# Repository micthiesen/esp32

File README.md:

# ESP32 Multi-Module Project

A modular ESP32 development environment with support for multiple main modules, configured for the Zed editor.

## Included Components

- **ESP-IDF v5.4** (as git submodule - ensures version consistency)
- **Build system** - CMake with multi-module support
- **Code quality** - clang-format, clang-tidy, clangd configuration with lint.sh
- **Zed integration** - Tasks, settings, and LSP setup
- **WiFi helper** - Secure credential management with wifi_helper component
- **Dynamic module selection** - Automatic discovery of main modules
- **Self-contained** - No global ESP-IDF installation required

## Project Structure

```
esp32/
├── .zed/                 # Zed editor configuration
│   ├── settings.json     # LSP and formatting settings
│   └── tasks.json        # Build/flash/monitor tasks
├── main/                 # Main modules directory
│   ├── main_blink.c      # LED blink example
│   ├── main_wifi.c       # WiFi connection example
│   ├── main_sensor.c     # Sensor reading example
│   └── wifi_config.h     # WiFi credentials (git-ignored)
├── components/           # Shared components
│   ├── helpers/          # Helper functions library
│   └── wifi_helper/      # WiFi connection component
├── CMakeLists.txt        # Root CMake configuration
├── .clang-format         # C/C++ formatting rules
├── .clangd               # LSP configuration
└── select_main.sh        # Module selection script
```

## Setup Instructions

### 1. Clone with Submodules

When cloning this repository, use `--recursive` to get the ESP-IDF submodule:

```bash
git clone --recursive <your-repo-url>
cd esp32
```

Or if you already cloned without `--recursive`:

```bash
git submodule update --init --recursive
```

### 2. Install ESP-IDF Tools

```bash
cd esp-idf
./install.sh esp32,esp32s3,esp32c3
cd ..
```

### 3. Set up Environment Alias

Add this to your shell profile (~/.zshrc or ~/.bashrc):

```bash
alias get_idf='. ./esp-idf/export.sh'
```

### 4. Initialize ESP-IDF for Each Session

Before working with ESP32, run (from project root):
```bash
get_idf
```

## Building Projects

### Method 1: Using Selection Script (Recommended)

```bash
./select_main.sh
# The script automatically discovers available modules
# Follow the prompts to select a module
# The selection is saved and persists across sessions
```

The script automatically discovers all `main_*.c` files and extracts descriptions from the code. No need to update the script when adding new modules!

### Method 2: Manual Module Selection

```bash
# Write the module name directly to the file
echo "wifi" > .main_module

# Then build normally
get_idf
idf.py build
```

### Method 3: Direct Build

The system automatically uses the currently selected module:

```bash
get_idf
idf.py build  # Uses whatever is in .main_module
```

## Zed Editor Tasks

Open the Command Palette (Cmd+Shift+P) and search for "task" to see available tasks:

### Build & Flash Tasks
- **Build** - Compile the current module
- **Flash** - Upload to ESP32
- **Monitor** - View serial output
- **Build & Flash** - Compile and upload
- **Build & Flash (Production)** - Optimized production build and flash
- **Build, Flash & Monitor** - All in one
- **Clean** - Remove build artifacts

### Module Management
- **Select Main Module** - Interactive module selection
- **Show Current Module** - Display currently selected module

### Configuration
- **Menuconfig** - Configure ESP32 settings
- **Set Target** - Switch between ESP32/ESP32-S3/ESP32-C3

### Analysis & Debug
- **Size Analysis** - Analyze binary size
- **Component Size Analysis** - Detailed size breakdown
- **Open Serial Monitor** - Monitor serial output
- **Erase Flash** - Completely erase flash memory

## Common Commands

```bash
# Set target chip
idf.py set-target esp32    # or esp32s3, esp32c3

# Configure project
idf.py menuconfig

# Build project
idf.py build

# Flash to device
idf.py flash

# Monitor serial output
idf.py monitor

# Combined commands
idf.py build flash monitor

# Clean build
idf.py fullclean

# Size analysis
idf.py size
idf.py size-components
```

## Module Selection System

The project uses a **file-based module selection** system:

- Current module is stored in `.main_module` file
- This file is user-specific (not committed to git)
- All build commands automatically use the selected module
- Module selection persists across terminal sessions and IDE restarts

### Current Module Status

```bash
# Check current module
cat .main_module

# Or use the task: "Show Current Module" in Zed
```

## Adding New Main Modules

1. Create a new file `main/main_yourmodule.c`
2. Include the app_main() function
3. Add a descriptive ESP_LOGI line (optional, for better descriptions):
   ```c
   ESP_LOGI(TAG, "Your module description starting...");
   ```
4. Select your module: `./select_main.sh` (it will auto-discover your new module)
5. Build: `idf.py build`

The module selection script automatically discovers new modules - no configuration needed!

## WiFi Module Configuration

The WiFi module uses a secure configuration system to keep credentials out of version control:

1. **Copy the template file:**
   ```bash
   cp main/wifi_config.h.template main/wifi_config.h
   ```

2. **Edit your WiFi credentials:**
   ```bash
   # Edit with your preferred editor
   nano main/wifi_config.h
   # or
   code main/wifi_config.h
   ```

3. **Update the configuration:**
   ```c
   #define WIFI_SSID "Your_Actual_WiFi_Name"
   #define WIFI_PASS "Your_Actual_Password"
   ```

4. **Build and flash:**
   ```bash
   idf.py build flash monitor
   ```

**Note:** The `wifi_config.h` file is git-ignored to keep your credentials secure. Each developer needs to create their own configuration file.

### Advanced WiFi Settings

You can customize additional WiFi parameters in `wifi_config.h`:

```c
// Connection settings
#define WIFI_MAX_RETRY 10                    // Retry attempts
#define WIFI_CONNECT_TIMEOUT_MS 15000        // Timeout in milliseconds

// Security settings
#define WIFI_AUTH_MODE WIFI_AUTH_WPA2_PSK    // Authentication mode
```

Available authentication modes:
- `WIFI_AUTH_OPEN` - No security (not recommended)
- `WIFI_AUTH_WEP` - WEP (legacy, not recommended)
- `WIFI_AUTH_WPA_PSK` - WPA-PSK
- `WIFI_AUTH_WPA2_PSK` - WPA2-PSK (recommended)
- `WIFI_AUTH_WPA2_WPA3_PSK` - WPA2/WPA3 mixed mode

## Troubleshooting

### Port Access Issues
If you get permission errors accessing the serial port:
```bash
sudo usermod -a -G dialout $USER  # Linux
# On macOS, the user should already have access
```

### Build Errors
1. Ensure ESP-IDF is sourced: `get_idf`
2. Clean and rebuild: `idf.py fullclean && idf.py build`
3. Check target matches your board: `idf.py set-target esp32`

### Zed LSP Issues
1. Ensure you've run the initial setup: `get_idf` from the project root
2. Restart Zed from the project directory: `zed .`
3. The project now uses a local ESP-IDF submodule for consistency

### Module Selection Issues
- If build fails with "No such file", check current module: `cat .main_module`
- Run `./select_main.sh` to select a valid module
- Verify the main file exists: `ls main/main_$(cat .main_module).c`

## Helper Functions

The `helpers` component provides utility functions:

- **Timing**: `delay_ms()`, `get_time_ms()`
- **LED Control**: `led_init()`, `led_on()`, `led_off()`, `led_toggle()`
- **Debug**: `hex_dump()`
- **Math**: `map_range()`, `constrain()`

Include in your module:
```c
#include "helpers.h"
```

## Code Quality and Linting

The project includes a comprehensive linting system to maintain code quality:

### Running Code Quality Checks

```bash
./lint.sh
```

The linting script performs:
- **Code formatting** with clang-format
- **Static analysis** with clang-tidy (filtered for ESP32 compatibility)
- **ESP32-specific checks** (WiFi config validation, header order)

### Integration with Development

- **Zed Editor**: Automatic formatting on save, real-time LSP feedback
- **Pre-commit**: Run `./lint.sh` before committing changes
- **CI/CD**: Include `./lint.sh` in your build pipeline

The linting configuration is designed to work seamlessly with ESP-IDF and filters out GCC-specific compiler flags that would cause issues with clang tools.

## Production Builds

The project supports optimized production builds with a single Zed task:

### Using Production Builds

**Via Zed Task**: Open Command Palette (Cmd+Shift+P) → "Build & Flash (Production)"

**Configuration**:
- Size optimization (`-Os`)
- Assertions disabled
- Error-only logging
- Each task uses its appropriate configuration (debug/production)

**When to Use**: For final deployment to production devices where code size and performance matter more than debugging capabilities.

## License

This project is licensed under the MIT License - see the [LICENSE](LICENSE) file for details.

The MIT License was chosen for its permissive nature, allowing both educational and commercial use while maintaining simplicity.

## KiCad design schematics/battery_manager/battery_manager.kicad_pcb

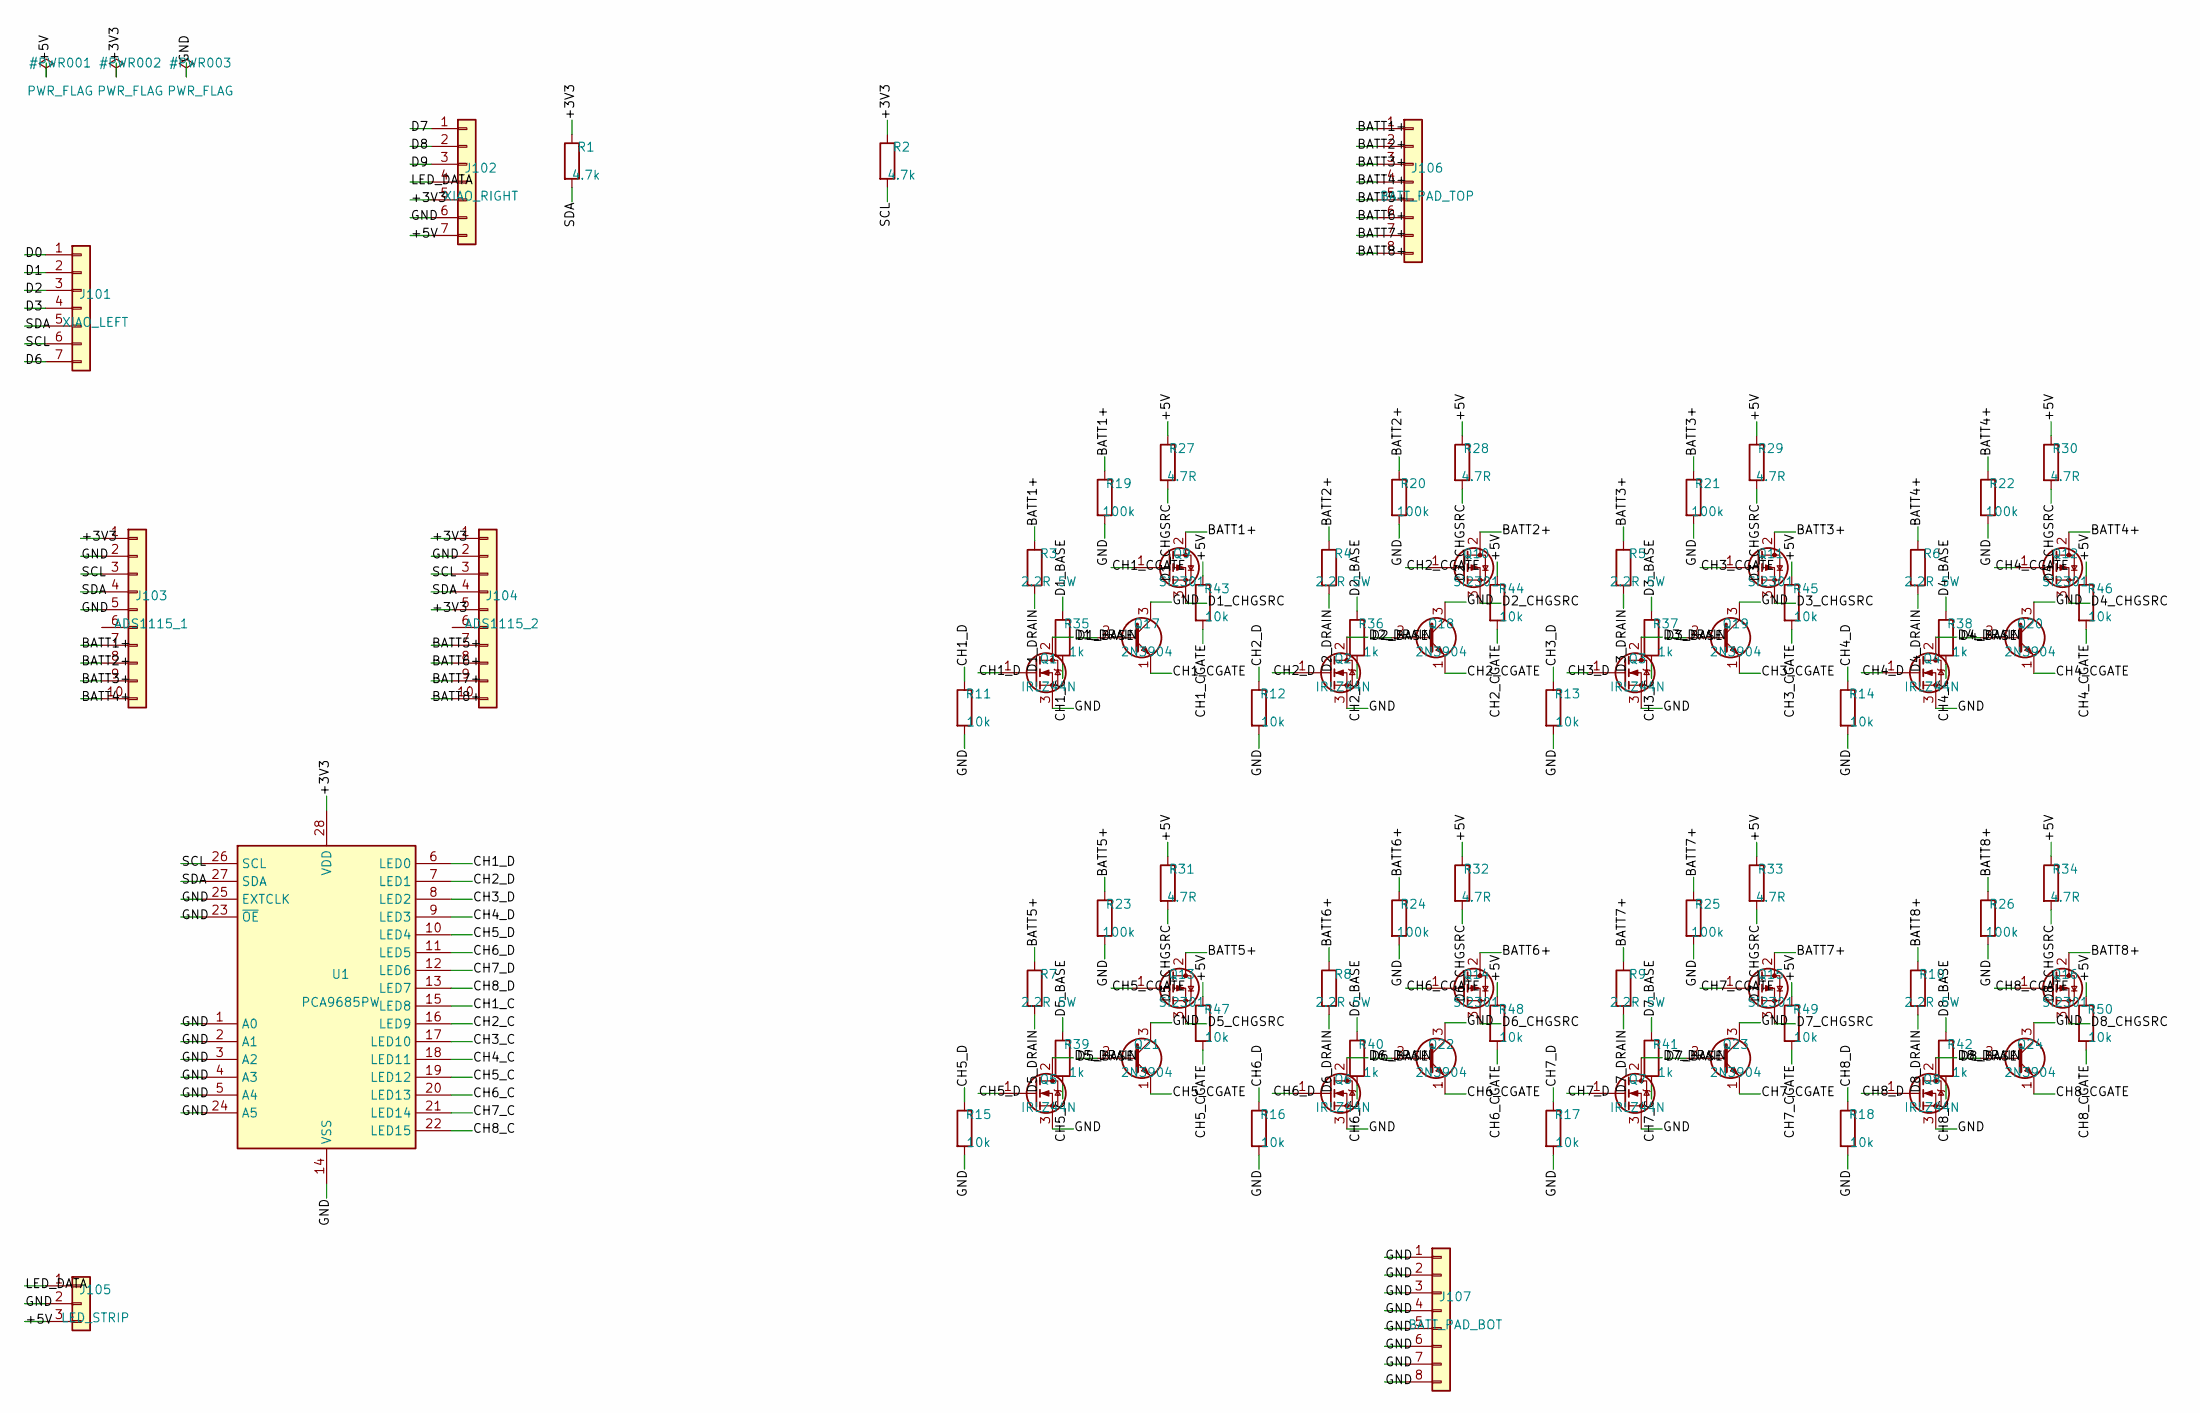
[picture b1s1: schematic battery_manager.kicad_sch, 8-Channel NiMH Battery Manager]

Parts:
J101: XIAO_LEFT; PinHeader_1x07_P2.54mm_Vertical
J102: XIAO_RIGHT; PinHeader_1x07_P2.54mm_Vertical
J103: ADS1115_1; PinHeader_1x10_P2.54mm_Vertical
J104: ADS1115_2; PinHeader_1x10_P2.54mm_Vertical
J105: LED_STRIP; PinHeader_1x03_P2.54mm_Vertical
J106: BATT_PAD_TOP; PinHeader_1x08_P2.54mm_Vertical
J107: BATT_PAD_BOT; PinHeader_1x08_P2.54mm_Vertical
Q1, Q2, Q3, Q4, Q5, Q6, Q7, Q8: IRLZ44N; TO-220-3_Vertical
Q9, Q10, Q11, Q12, Q13, Q14, Q15, Q16: Si2301; SOT-23
Q17, Q18, Q19, Q20, Q21, Q22, Q23, Q24: 2N3904; TO-92_Inline
R1, R2: 4.7k; R_Axial_DIN0207_L6.3mm_D2.5mm_P10.16mm_Horizontal
R3, R4, R5, R6, R7, R8, R9, R10: 2.2R 5W; R_Axial_DIN0617_L17.0mm_D6.0mm_P25.40mm_Horizontal
R11, R12, R13, R14, R15, R16, R17, R18, R43, R44, R45, R46, R47, R48, R49, R50: 10k; R_Axial_DIN0207_L6.3mm_D2.5mm_P10.16mm_Horizontal
R19, R20, R21, R22, R23, R24, R25, R26: 100k; R_Axial_DIN0207_L6.3mm_D2.5mm_P10.16mm_Horizontal
R27, R28, R29, R30, R31, R32, R33, R34: 4.7R; R_Axial_DIN0207_L6.3mm_D2.5mm_P10.16mm_Horizontal
R35, R36, R37, R38, R39, R40, R41, R42: 1k; R_Axial_DIN0207_L6.3mm_D2.5mm_P10.16mm_Horizontal
U1: PCA9685PW; TSSOP-28_4.4x9.7mm_P0.65mm

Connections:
/BATT1+: J103.7, J106.1, Q9.2 (D), R3.1, R19.1
/BATT2+: J103.8, J106.2, Q10.2 (D), R4.1, R20.1
/BATT3+: J103.9, J106.3, Q11.2 (D), R5.1, R21.1
/BATT4+: J103.10, J106.4, Q12.2 (D), R6.1, R22.1
/BATT5+: J104.7, J106.5, Q13.2 (D), R7.1, R23.1
/BATT6+: J104.8, J106.6, Q14.2 (D), R8.1, R24.1
/BATT7+: J104.9, J106.7, Q15.2 (D), R9.1, R25.1
/BATT8+: J104.10, J106.8, Q16.2 (D), R10.1, R26.1
/CH1_C: R35.2, U1.15 (LED8)
/CH1_CGATE: Q9.1 (G), Q17.1 (E), R43.2
/CH1_D: Q1.1 (G), R11.1, U1.6 (LED0)
/CH2_C: R36.2, U1.16 (LED9)
/CH2_CGATE: Q10.1 (G), Q18.1 (E), R44.2
/CH2_D: Q2.1 (G), R12.1, U1.7 (LED1)
/CH3_C: R37.2, U1.17 (LED10)
/CH3_CGATE: Q11.1 (G), Q19.1 (E), R45.2
/CH3_D: Q3.1 (G), R13.1, U1.8 (LED2)
/CH4_C: R38.2, U1.18 (LED11)
/CH4_CGATE: Q12.1 (G), Q20.1 (E), R46.2
/CH4_D: Q4.1 (G), R14.1, U1.9 (LED3)
/CH5_C: R39.2, U1.19 (LED12)
/CH5_CGATE: Q13.1 (G), Q21.1 (E), R47.2
/CH5_D: Q5.1 (G), R15.1, U1.10 (LED4)
/CH6_C: R40.2, U1.20 (LED13)
/CH6_CGATE: Q14.1 (G), Q22.1 (E), R48.2
/CH6_D: Q6.1 (G), R16.1, U1.11 (LED5)
/CH7_C: R41.2, U1.21 (LED14)
/CH7_CGATE: Q15.1 (G), Q23.1 (E), R49.2
/CH7_D: Q7.1 (G), R17.1, U1.12 (LED6)
/CH8_C: R42.2, U1.22 (LED15)
/CH8_CGATE: Q16.1 (G), Q24.1 (E), R50.2
/CH8_D: Q8.1 (G), R18.1, U1.13 (LED7)
/D0: J101.1
/D1: J101.2
/D1_BASE: Q17.2 (B), R35.1
/D1_CHGSRC: Q9.3 (S), R27.2
/D1_DRAIN: Q1.2 (D), R3.2
/D2: J101.3
/D2_BASE: Q18.2 (B), R36.1
/D2_CHGSRC: Q10.3 (S), R28.2
/D2_DRAIN: Q2.2 (D), R4.2
/D3: J101.4
/D3_BASE: Q19.2 (B), R37.1
/D3_CHGSRC: Q11.3 (S), R29.2
/D3_DRAIN: Q3.2 (D), R5.2
/D4_BASE: Q20.2 (B), R38.1
/D4_CHGSRC: Q12.3 (S), R30.2
/D4_DRAIN: Q4.2 (D), R6.2
/D5_BASE: Q21.2 (B), R39.1
/D5_CHGSRC: Q13.3 (S), R31.2
/D5_DRAIN: Q5.2 (D), R7.2
/D6: J101.7
/D6_BASE: Q22.2 (B), R40.1
/D6_CHGSRC: Q14.3 (S), R32.2
/D6_DRAIN: Q6.2 (D), R8.2
/D7: J102.1
/D7_BASE: Q23.2 (B), R41.1
/D7_CHGSRC: Q15.3 (S), R33.2
/D7_DRAIN: Q7.2 (D), R9.2
/D8: J102.2
/D8_BASE: Q24.2 (B), R42.1
/D8_CHGSRC: Q16.3 (S), R34.2
/D8_DRAIN: Q8.2 (D), R10.2
/D9: J102.3
/LED_DATA: J102.4, J105.1
/SCL: J101.6, J103.3, J104.3, R2.2, U1.26 (SCL)
/SDA: J101.5, J103.4, J104.4, R1.2, U1.27 (SDA)

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
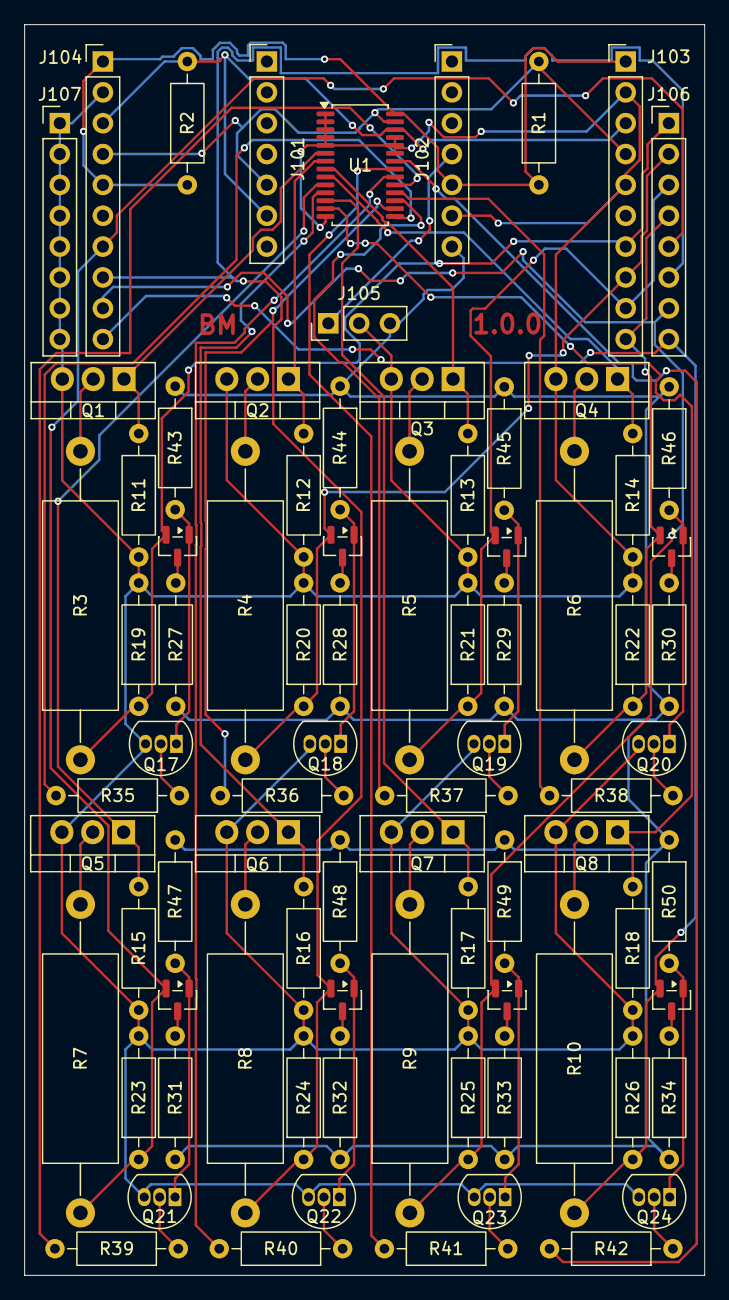
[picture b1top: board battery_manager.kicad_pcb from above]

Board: 2 copper layers, 56.0 x 103.0 mm, 82 parts (0 on the bottom side), 62 nets.

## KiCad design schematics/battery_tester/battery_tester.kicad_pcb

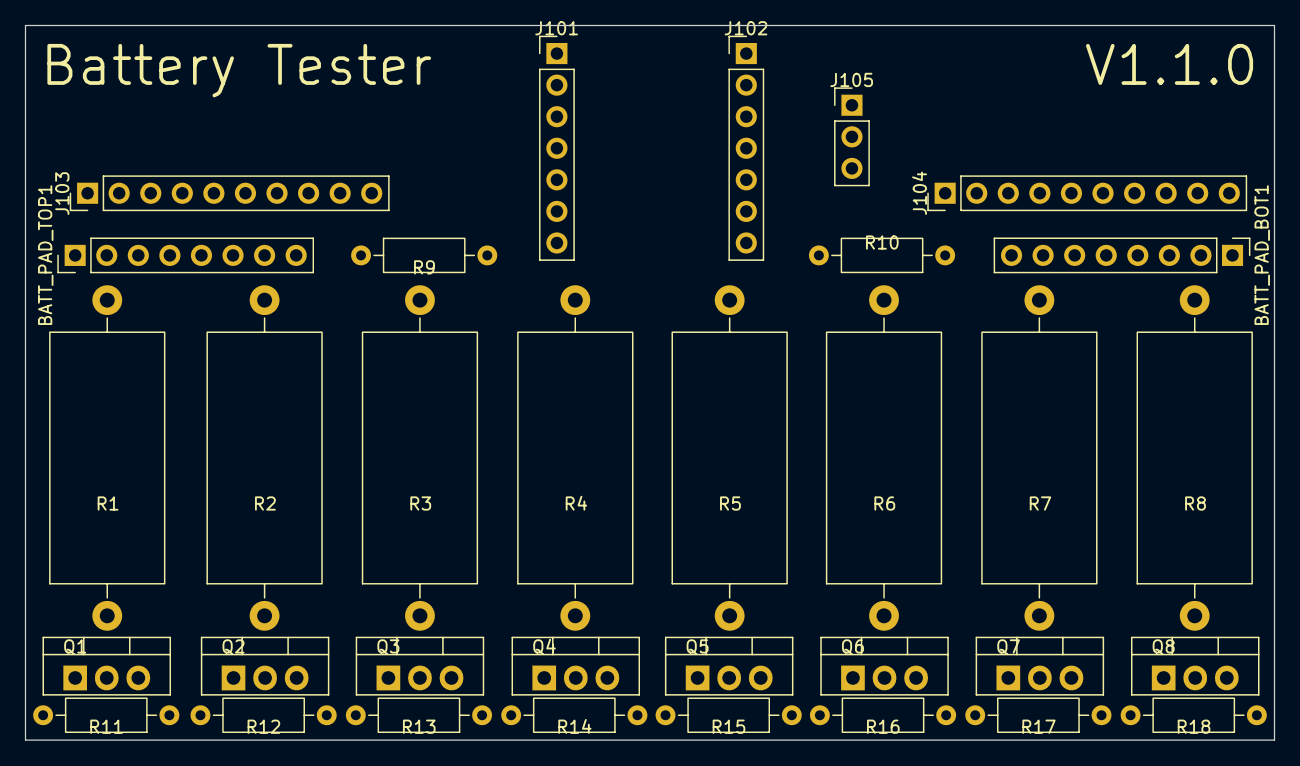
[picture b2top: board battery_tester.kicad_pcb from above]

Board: 2 copper layers, 100.5 x 57.5 mm, 33 parts (0 on the bottom side), 26 nets, no tracks yet.

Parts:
BATT_PAD_BOT1: Conn_01x08; PinHeader_1x08_P2.54mm_Vertical
BATT_PAD_TOP1: Conn_01x08; PinHeader_1x08_P2.54mm_Vertical
J101: XIAO_LEFT; PinHeader_1x07_P2.54mm_Vertical
J102: XIAO_RIGHT; PinHeader_1x07_P2.54mm_Vertical
J103: ADS1115_1; PinHeader_1x10_P2.54mm_Vertical
J104: ADS1115_2; PinHeader_1x10_P2.54mm_Vertical
J105: LED_STRIP; PinHeader_1x03_P2.54mm_Vertical
Q1, Q2, Q3, Q4, Q5, Q6, Q7, Q8: IRLZ44N; TO-220-3_Vertical
R1, R2, R3, R4, R5, R6, R7, R8: 2.2R 5W; R_Axial_DIN0922_L20.0mm_D9.0mm_P25.40mm_Horizontal
R9, R10: 4.7k; R_Axial_DIN0207_L6.3mm_D2.5mm_P10.16mm_Horizontal
R11, R12, R13, R14, R15, R16, R17, R18: 10k; R_Axial_DIN0207_L6.3mm_D2.5mm_P10.16mm_Horizontal

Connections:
/+3V3: R9.2, R10.2
/BATT1+: BATT_PAD_TOP1.3, R1.2
/BATT2+: BATT_PAD_BOT1.5, R2.2
/BATT3+: BATT_PAD_TOP1.5, R3.2
/BATT4+: BATT_PAD_BOT1.3, R4.2
/BATT5+: BATT_PAD_TOP1.1, R5.2
/BATT6+: BATT_PAD_BOT1.7, R6.2
/BATT7+: BATT_PAD_TOP1.7, R7.2
/BATT8+: BATT_PAD_BOT1.1, R8.2
/CH1_D: Q1.2 (D), R1.1
/CH2_D: Q2.2 (D), R2.1
/CH3_D: Q3.2 (D), R3.1
/CH4_D: Q4.2 (D), R4.1
/CH5_D: Q5.2 (D), R5.1
/CH6_D: Q6.2 (D), R6.1
/CH7_D: Q7.2 (D), R7.1
/CH8_D: Q8.2 (D), R8.1
/GND: BATT_PAD_BOT1.2, BATT_PAD_BOT1.4, BATT_PAD_BOT1.6, BATT_PAD_BOT1.8, BATT_PAD_TOP1.2, BATT_PAD_TOP1.4, BATT_PAD_TOP1.6, BATT_PAD_TOP1.8, Q1.3 (S), Q2.3 (S), Q3.3 (S), Q4.3 (S), Q5.3 (S), Q6.3 (S), Q7.3 (S), Q8.3 (S), R11.1, R12.1, R13.1, R14.1, R15.1, R16.1, R17.1, R18.1
/GPIO2: Q1.1 (G), R11.2
/GPIO3: Q2.1 (G), R12.2
/GPIO4: Q3.1 (G), R13.2
/GPIO5: Q4.1 (G), R14.2
/GPIO8: Q5.1 (G), R15.2
/GPIO9: Q6.1 (G), R16.2
/GPIO10: Q7.1 (G), R17.2
/GPIO20: Q8.1 (G), R18.2

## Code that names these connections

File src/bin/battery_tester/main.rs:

#![no_std]
#![no_main]

esp_bootloader_esp_idf::esp_app_desc!();

mod channel;
mod config;
mod led;
mod notify;
mod serial;

use embassy_sync::blocking_mutex::raw::CriticalSectionRawMutex;
use embassy_sync::channel::{Channel, Sender};
use embassy_time::{Duration, Timer};
use esp_backtrace as _;
use esp_hal::gpio::{Level, Output, OutputConfig, Pin};
use esp_hal::i2c::master::{Config as I2cConfig, I2c};
use esp_hal::rmt::Rmt;
use esp_hal::time::Rate;
use esp_hal::timer::timg::TimerGroup;
use esp_hal::usb_serial_jtag::UsbSerialJtag;
use firmware::adc::{BatteryAdc, SharedI2cBus};
use static_cell::StaticCell;

use crate::channel::{Action, ChannelCtx, ChannelState, Notification, NotifyChannel, SharedState};
use crate::config::{SlotType, NUM_CHANNELS};
use crate::serial::SerialCommand;

type I2cBus = I2c<'static, esp_hal::Blocking>;

#[esp_rtos::main]
async fn main(spawner: embassy_executor::Spawner) {
    esp_println::logger::init_logger_from_env();

    let peripherals = esp_hal::init(esp_hal::Config::default());

    let timg0 = TimerGroup::new(peripherals.TIMG0);
    let sw_int =
        esp_hal::interrupt::software::SoftwareInterruptControl::new(peripherals.SW_INTERRUPT);
    esp_rtos::start(timg0.timer0, sw_int.software_interrupt0);

    log::info!("Battery capacity tester starting up");

    // Initialize I2C bus for ADS1115 communication
    let i2c = I2c::new(peripherals.I2C0, I2cConfig::default())
        .unwrap()
        .with_sda(peripherals.GPIO6)
        .with_scl(peripherals.GPIO7);

    static I2C_BUS: StaticCell<SharedI2cBus<I2cBus>> = StaticCell::new();
    let i2c_bus: &'static SharedI2cBus<I2cBus> =
        I2C_BUS.init(critical_section::Mutex::new(core::cell::RefCell::new(i2c)));

    // Initialize MOSFET gate pins as output LOW (discharge disabled)
    let mosfet_pins: [Output<'static>; 8] = [
        Output::new(peripherals.GPIO2, Level::Low, OutputConfig::default()),
        Output::new(peripherals.GPIO3, Level::Low, OutputConfig::default()),
        Output::new(peripherals.GPIO4, Level::Low, OutputConfig::default()),
        Output::new(peripherals.GPIO5, Level::Low, OutputConfig::default()),
        Output::new(peripherals.GPIO8, Level::Low, OutputConfig::default()),
        Output::new(peripherals.GPIO9, Level::Low, OutputConfig::default()),
        Output::new(peripherals.GPIO10, Level::Low, OutputConfig::default()),
        Output::new(peripherals.GPIO20, Level::Low, OutputConfig::default()),
    ];

    static STATE: StaticCell<SharedState> = StaticCell::new();
    let state: &'static SharedState = STATE.init(embassy_sync::mutex::Mutex::new(
        [ChannelState::Idle; NUM_CHANNELS],
    ));

    static CMD_CHAN: StaticCell<Channel<CriticalSectionRawMutex, SerialCommand, 4>> =
        StaticCell::new();
    let cmd_chan: &'static Channel<CriticalSectionRawMutex, SerialCommand, 4> =
        CMD_CHAN.init(Channel::new());

    let rmt = Rmt::new(peripherals.RMT, Rate::from_mhz(80)).unwrap();

    let usb_serial = UsbSerialJtag::new(peripherals.USB_DEVICE);

    // Spawn core tasks first (LEDs, serial, channel manager) so they start immediately
    spawner
        .spawn(led::led_task(
            rmt.channel0,
            peripherals.GPIO21.degrade(),
            state,
        ))
        .unwrap();
    spawner
        .spawn(serial::serial_task(usb_serial, state, cmd_chan.sender()))
        .unwrap();

    static NOTIFY_CHAN: StaticCell<NotifyChannel> = StaticCell::new();
    let notify_chan: &'static NotifyChannel = NOTIFY_CHAN.init(Channel::new());
    let notify_tx = Some(notify_chan.sender());

    spawner
        .spawn(channel_manager(
            mosfet_pins,
            i2c_bus,
            state,
            cmd_chan.receiver(),
            notify_tx,
        ))
        .unwrap();

    log::info!("Battery capacity tester ready");

    // Initialize WiFi and notifications in background (never blocks core tasks)
    esp_alloc::heap_allocator!(size: 72 * 1024);

    let stack = firmware::wifi::init(&spawner, peripherals.WIFI).await;

    spawner
        .spawn(notify::notify_task(stack, notify_chan.receiver()))
        .unwrap();
}

#[embassy_executor::task]
async fn channel_manager(
    mut mosfets: [Output<'static>; 8],
    i2c_bus: &'static SharedI2cBus<I2cBus>,
    state: &'static SharedState,
    cmd_rx: embassy_sync::channel::Receiver<'static, CriticalSectionRawMutex, SerialCommand, 4>,
    notify_tx: Option<Sender<'static, CriticalSectionRawMutex, Notification, 8>>,
) {
    let mut battery_adc = BatteryAdc::new(i2c_bus);
    let mut channels: [ChannelCtx; 8] = core::array::from_fn(|_| ChannelCtx::new());

    loop {
        Timer::after(Duration::from_millis(config::SAMPLE_INTERVAL_MS)).await;

        // Check for serial commands
        if let Ok(cmd) = cmd_rx.try_receive() {
            match cmd {
                SerialCommand::Stop => {
                    log::info!("STOP received, stopping all channels");
                    for slot in 0..NUM_CHANNELS {
                        let action = channels[slot].stop();
                        if matches!(action, Action::DisableMosfet) {
                            mosfets[slot].set_low();
                        }
                    }
                }
                SerialCommand::StopSlot(n) => {
                    if n < NUM_CHANNELS {
                        log::info!("STOP received for slot {}", n + 1);
                        let action = channels[n].stop();
                        if matches!(action, Action::DisableMosfet) {
                            mosfets[n].set_low();
                        }
                    }
                }
                _ => {}
            }
        }

        // Read all 8 ADC channels and update state machines
        for slot in 0..NUM_CHANNELS {
            let voltage = battery_adc.read_voltage(slot as u8).map_err(|_| ());
            let action = channels[slot].update(voltage, slot);

            match action {
                Action::EnableMosfet => {
                    mosfets[slot].set_high();
                }
                Action::DisableMosfet => {
                    mosfets[slot].set_low();
                }
                Action::Terminal(kind) => {
                    mosfets[slot].set_low();
                    if let Some(ref tx) = notify_tx {
                        let _ = tx.try_send(Notification {
                            slot: (slot + 1) as u8,
                            slot_type: SlotType::from_slot(slot),
                            kind,
                        });
                    }
                }
                Action::None => {}
            }
        }

        // Update shared state (single lock for all 8 slots)
        let mut shared = state.lock().await;
        for slot in 0..NUM_CHANNELS {
            shared[slot] = channels[slot].state();
        }
    }
}

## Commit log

2025-09-14 Nice ESP32 dev env
2025-09-14 Add comprehensive ESP32 development guidelines for Claude
2025-09-14 Add debug and production build configurations
2025-09-15 Integrate ESP-Matter and add Matter temperature sensor example
2025-09-15 Conditionally add esp_matter dependency for Matter module
2025-09-15 Remove esp-matter submodule (heavy recursive checkout)
2025-09-15 Re-add esp-matter submodule shallow/filtered
2025-09-15 Remove specific file scan exclusions
2025-09-15 Implement real Matter temperature sensor
2025-09-15 Simplify Matter commissioning logic
2025-09-15 Simplify component management for Matter projects
2025-09-15 Switch to global ESP-IDF and ESP-Matter installations
2025-09-15 Simplify ESP-IDF path configuration and Zed tasks
2025-09-15 Improve module detection in configure.sh
2025-09-15 Allow git lfs pull and add Matter config components
2025-09-15 Integrate esp-matter via component manager
2025-09-15 Configure Matter projects with correct partition table
2025-09-15 Consolidate Matter-related configs into sdkconfig.defaults
2025-09-15 Display Matter commissioning QR code and manual code
2025-09-15 Include RendezvousParameters header
2025-09-16 Update clangd config and Matter sensor code
2025-09-16 Clean project in preparation for Rust
2025-09-16 Add rust template stuff
2025-09-16 Rename CI workflow file to standard path
2025-09-16 Add Zed tasks and Claude permissions for ESP32 development
2025-09-16 Implement basic LED blinking example
2025-09-16 Rename Claude task command to 'claude'
2025-09-16 Remove redundant 'cargo run' task
2025-09-17 Introduce modular application structure and common utilities
2025-09-17 Add compile-time configuration via config.toml
2025-09-17 Add WiFi test application
2025-09-17 Configure large single app partition for 4MB flash
2025-09-17 Format code for improved readability
2025-09-17 Enable Rust format on save in Zed settings
2025-09-17 Copy example config for CI build
2026-03-22 Rewrite project as 8-channel NiMH battery capacity tester
    Replace the previous blink/WiFi test scaffolding with a complete
    battery capacity tester firmware targeting ESP32-C3 with esp-hal 1.0.
    Hardware: 2x ADS1115 ADCs, 8x IRLZ44N MOSFET discharge switches,
    SK6812 addressable LEDs for status, all on ESP32-C3.
    Firmware features:
    - Embassy async tasks for concurrent 8-channel discharge management
2026-03-22 Refactor into multi-binary project with shared lib
    Restructure the project to support multiple binaries (`battery-tester`
    and `blink`) by moving shared logic into a library crate. Feature-gate
    WiFi and networking dependencies to allow for more lightweight builds.
2026-03-22 Implement continuous per-channel battery testing
    Each slot now operates an independent state machine that automatically
    detects, scans, and discharges batteries upon insertion. Removed the
    manual START command in favor of autonomous operation and added Wokwi
    simulation support.
2026-03-22 Add wiring checklist for protoboard build
    Markdown checklist organized by soldering phase with per-connection
    rows showing Device/Pin on each side and a column for wire colors.
    Also add .venv to gitignore.
2026-03-22 Add print script for wiring checklist PDF
    bash docs/print.sh --open to generate and view the PDF.
    Shorten ADC labels, gitignore generated PDFs.
2026-03-22 Update hardware design to KiCad and optimize pinout
    - Migrate manual wiring checklist to KiCad schematics and PCB layout -
    Reassign I2C and discharge control pins for better routing - Switch
    serial output to JTAG/serial for ESP32-C3 compatibility - Remove
    obsolete documentation and print scripts - Update Wokwi simulation
    diagram to match new pinout
2026-03-22 Remove Wokwi simulation and make WiFi mandatory
    Eliminates the custom ADS1115 C simulation, Wokwi configuration files,
    and the 'wifi' feature gate. WiFi and networking are now core
    requirements for the battery tester firmware.
2026-03-22 Ignore lock files and update PCB layout
2026-04-03 Add v1.0.0 PCB layout with routed board and gerber outputs
2026-04-03 Fix CI: add RISC-V target, correct config path, remove ESP-IDF leftovers
2026-04-03 Remove CI workflow
2026-04-04 Add ADC test utility and update PCB layout
    Introduces a new binary to validate battery voltage readings via I2C
    and updates the hardware schematics for the battery tester.
2026-04-04 Add serial monitor script and raise empty slot voltage threshold
2026-04-04 Make serial monitor script executable
2026-04-04 Implement background serial monitoring and RGBW support
    Introduces a daemonized serial monitor with lock-file arbitration
    for flashing, adds an LED color test binary, and updates the battery
    tester to support SK6812W RGBW LEDs with corrected color ordering. Also
    improves WiFi resilience by making the initial connection non-blocking.
2026-04-05 Update battery tester hardware and LED logic
    Major revision to KiCad schematics and PCB layout (v2.0). Refines LED
    behavior by reducing brightness, removing flashing for weak batteries in
    favor of a solid color, and wrapping LED writes in a critical section.
2026-04-05 Defer WiFi initialization to prevent blocking boot
    Move WiFi and notification setup after core hardware tasks to ensure
    the device remains responsive during network negotiation. This prevents
    slow DHCP or connection retries from delaying the startup of LEDs,
    serial communication, and the channel manager.
2026-04-06 Add battery manager hardware and breathing LEDs
    Initial commit of the battery manager KiCad project, including
    schematics, PCB layout, and BOM. Updated the battery tester firmware
    to replace discrete LED blinking with a smooth breathing effect.
